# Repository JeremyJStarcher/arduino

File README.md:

# arduino
Random Arduino related things.

Some of these are better documented than others, but I figured it was better
to have one big repo rather than clutter things with a dozen small ones.

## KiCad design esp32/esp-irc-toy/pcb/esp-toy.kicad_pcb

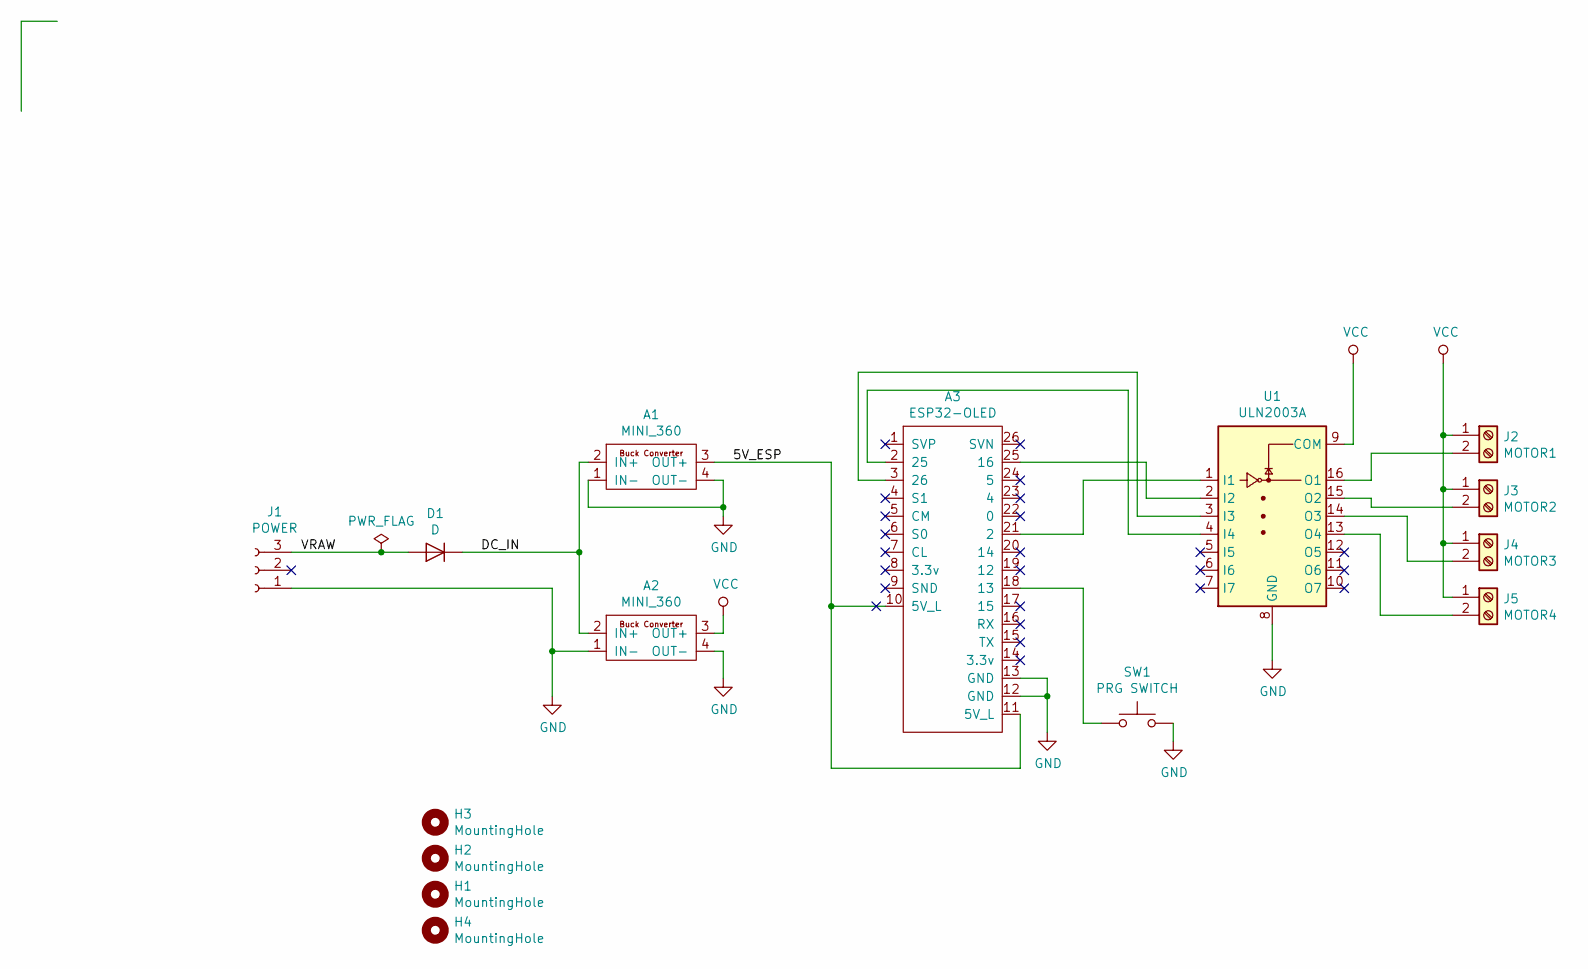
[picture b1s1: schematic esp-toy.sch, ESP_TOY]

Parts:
A1, A2: MINI_360
A3: ESP32-OLED
D1: D; D_5W_P12.70mm_Horizontal
H1, H2, H3, H4: MountingHole; MountingHole_2.2mm_M2_DIN965_Pad
J1: POWER; PinSocket_1x03_P2.54mm_Horizontal
J2: MOTOR1; TerminalBlock_bornier-2_P5.08mm
J3: MOTOR2; TerminalBlock_bornier-2_P5.08mm
J4: MOTOR3; TerminalBlock_bornier-2_P5.08mm
J5: MOTOR4; TerminalBlock_bornier-2_P5.08mm
SW1: PRG SWITCH; SW_PUSH-12mm
U1: ULN2003A; DIP-16_W10.16mm

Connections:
/5V_2: A1.3 (OUT+), A3.10 (5V_L), A3.11 (5V_L)
/DC_IN: A1.2 (IN+), A2.2 (IN+), D1.1 (K)
/VRAW: D1.2 (A), J1.3
GND: A1.1 (IN-), A1.4 (OUT-), A2.1 (IN-), A2.4 (OUT-), A3.12 (GND), A3.13 (GND), J1.1, SW1.2, U1.8 (GND)
unnamed: A3.2 (25), U1.4 (I4)
unnamed: A3.3 (26), U1.3 (I3)
unnamed: A3.18 (13), SW1.1
unnamed: A3.21 (2), U1.1 (I1)
unnamed: A3.25 (16), U1.2 (I2)
unnamed: J2.2, U1.16 (O1)
unnamed: J3.2, U1.15 (O2)
unnamed: J4.2, U1.14 (O3)
unnamed: J5.2, U1.13 (O4)
VCC: A2.3 (OUT+), J2.1, J3.1, J4.1, J5.1, U1.9 (COM)

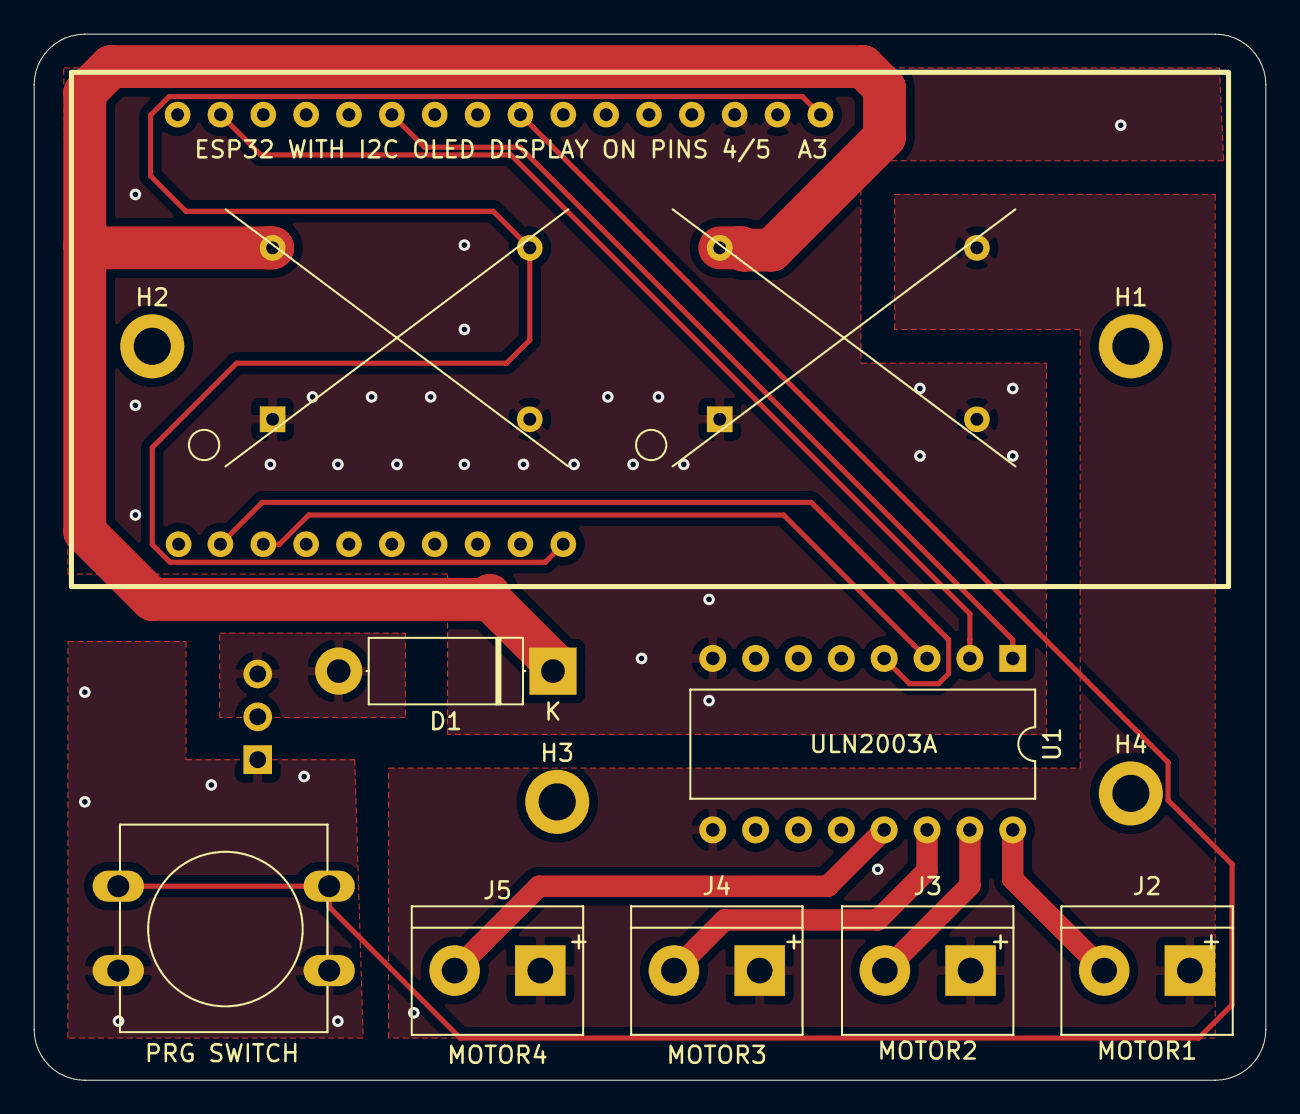
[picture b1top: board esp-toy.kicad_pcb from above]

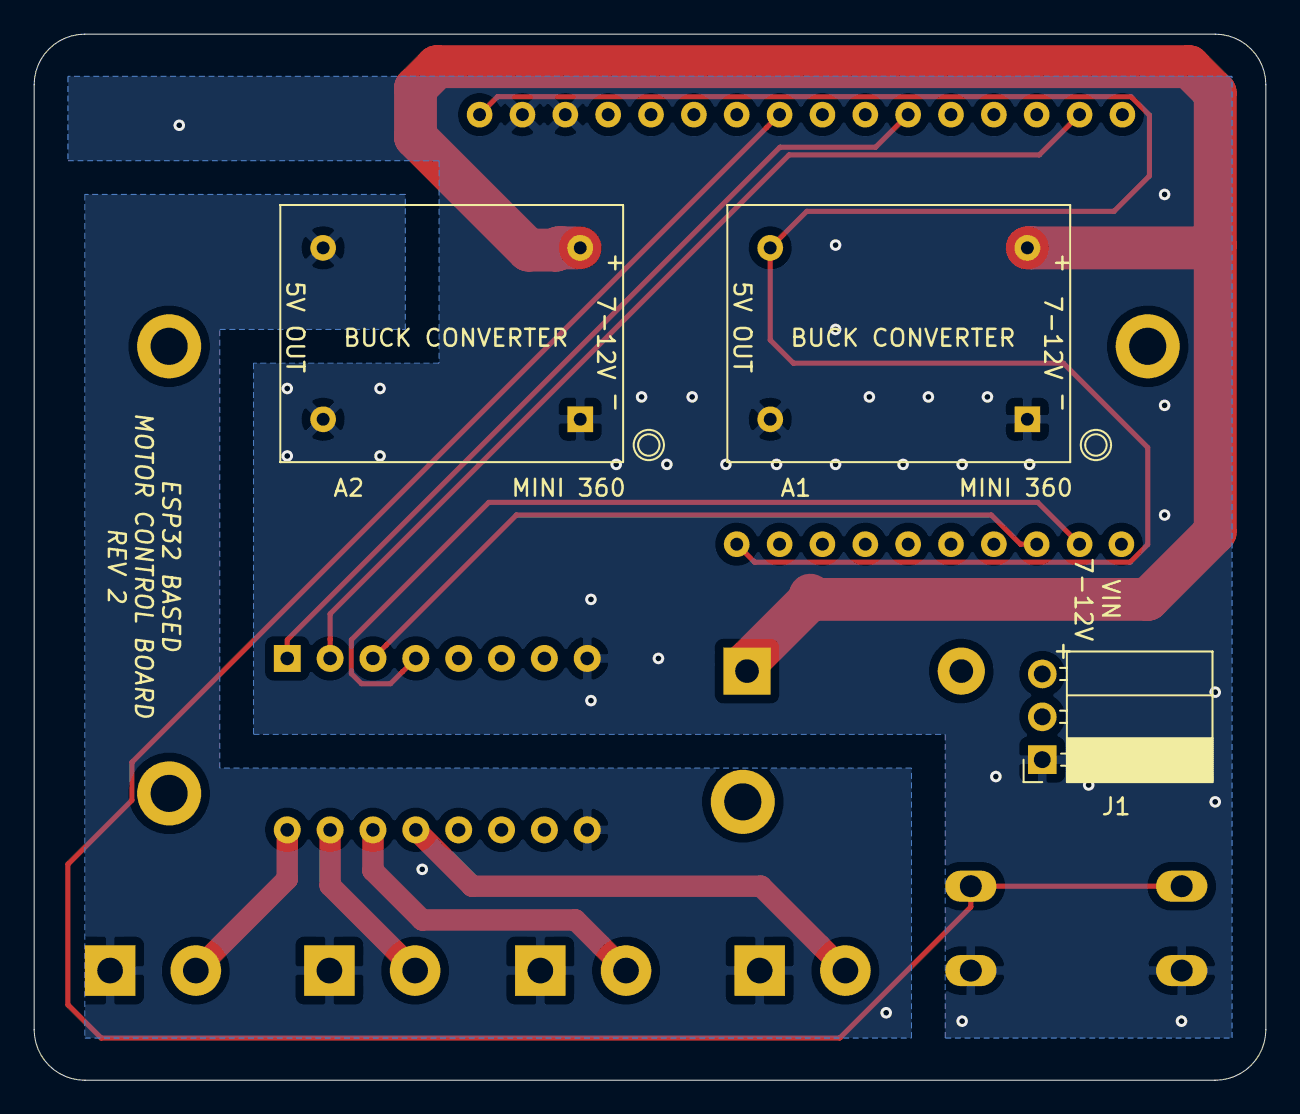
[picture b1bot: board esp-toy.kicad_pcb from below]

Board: 2 copper layers, 73.0 x 62.0 mm, 15 parts (3 on the bottom side), 14 nets.

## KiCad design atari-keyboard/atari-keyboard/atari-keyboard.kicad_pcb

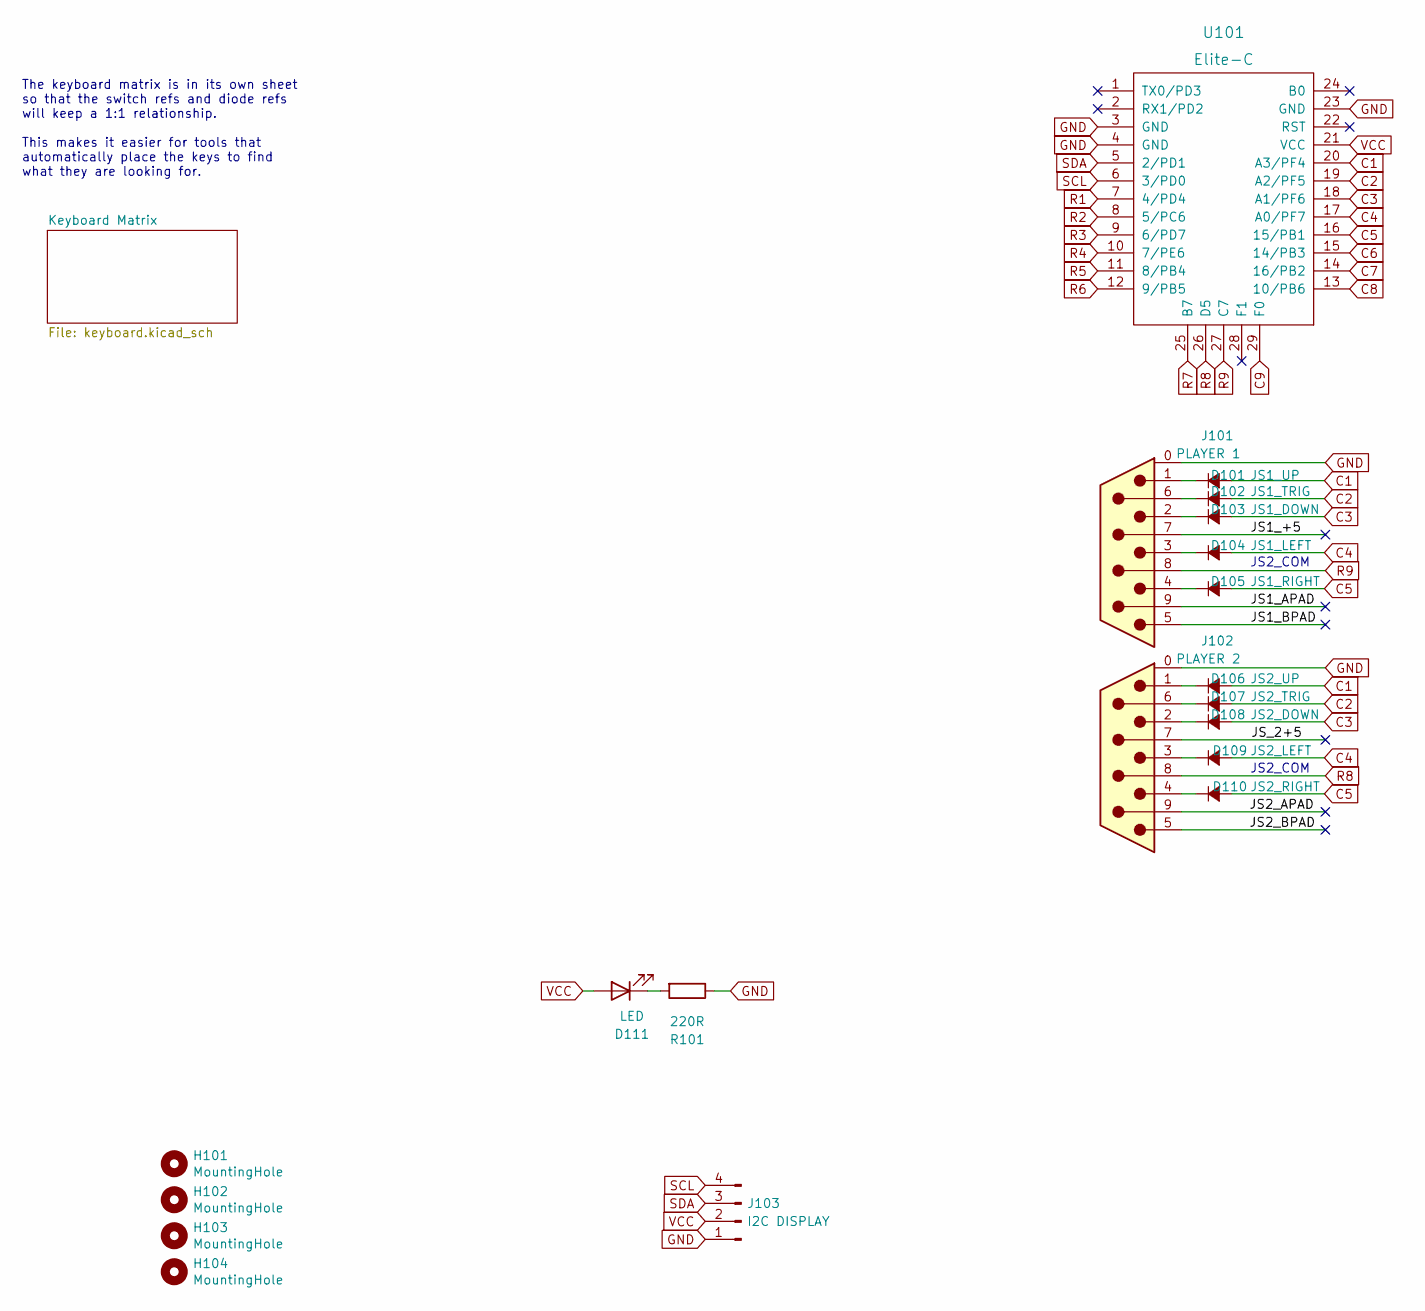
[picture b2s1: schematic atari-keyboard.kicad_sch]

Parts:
D101: JS1_UP; Diode-dual
D102: JS1_TRIG; Diode-dual
D103: JS1_DOWN; Diode-dual
D104: JS1_LEFT; Diode-dual
D105: JS1_RIGHT; Diode-dual
D106: JS2_UP; Diode-dual
D107: JS2_TRIG; Diode-dual
D108: JS2_DOWN; Diode-dual
D109: JS2_LEFT; Diode-dual
D110: JS2_RIGHT; Diode-dual
D111: LED; LED_D3.0mm
H101, H102, H103, H104: MountingHole; MountingHole_3.2mm_M3
J101: PLAYER 1; DSUB-9_Male_Horizontal_P2.77x2.84mm_EdgePinOffset9.90mm_Hou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
J102: PLAYER 2; DSUB-9_Male_Horizontal_P2.77x2.84mm_EdgePinOffset9.90mm_Hou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
J103: I2C DISPLAY; PinHeader_1x04_P2.54mm_Horizontal
R101: 220R; Resistor-Hybrid
U101: Elite-C; Elite-C-castellated-29pin-holes

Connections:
/JS1_+5: J101.7
/JS1_APAD: J101.9
/JS1_BPAD: J101.5
/JS2_APAD: J102.9
/JS2_BPAD: J102.5
/JS_2+5: J102.7
C1: D101.2 (A), D106.2 (A), U101.20 (A3/PF4); also elsewhere on the board
C2: D102.2 (A), D107.2 (A), U101.19 (A2/PF5); also elsewhere on the board
C3: D103.2 (A), D108.2 (A), U101.18 (A1/PF6); also elsewhere on the board
C4: D104.2 (A), D109.2 (A), U101.17 (A0/PF7); also elsewhere on the board
C5: D105.2 (A), D110.2 (A), U101.16 (15/PB1); also elsewhere on the board
C6: U101.15 (14/PB3); also elsewhere on the board
C7: U101.14 (16/PB2); also elsewhere on the board
C8: U101.13 (10/PB6); also elsewhere on the board
C9: U101.29 (F0); also elsewhere on the board
GND: J101.0 (GND), J102.0 (GND), J103.1, R101.1, U101.3 (GND), U101.4 (GND), U101.23 (GND)
unnamed: D101.1 (K), J101.1
unnamed: D102.1 (K), J101.6
unnamed: D103.1 (K), J101.2
unnamed: D104.1 (K), J101.3
unnamed: D105.1 (K), J101.4
unnamed: D106.1 (K), J102.1
unnamed: D107.1 (K), J102.6
unnamed: D108.1 (K), J102.2
unnamed: D109.1 (K), J102.3
unnamed: D110.1 (K), J102.4
unnamed: D111.1 (K), R101.2
R1: U101.7 (4/PD4); also elsewhere on the board
R2: U101.8 (5/PC6); also elsewhere on the board
R3: U101.9 (6/PD7); also elsewhere on the board
R4: U101.10 (7/PE6); also elsewhere on the board
R5: U101.11 (8/PB4); also elsewhere on the board
R6: U101.12 (9/PB5); also elsewhere on the board
R7: U101.25 (B7); also elsewhere on the board
R8: J102.8, U101.26 (D5); also elsewhere on the board
R9: J101.8, U101.27 (C7); also elsewhere on the board
SCL: J103.4, U101.6 (3/PD0)
SDA: J103.3, U101.5 (2/PD1)
VCC: D111.2 (A), J103.2, U101.21 (VCC)

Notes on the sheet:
JS2_COM
The keyboard matrix is in its own sheet so that the switch refs and diode refs will keep a 1:1 relationship. This makes it easier for tools that automatically place the keys to find what they are looking for.

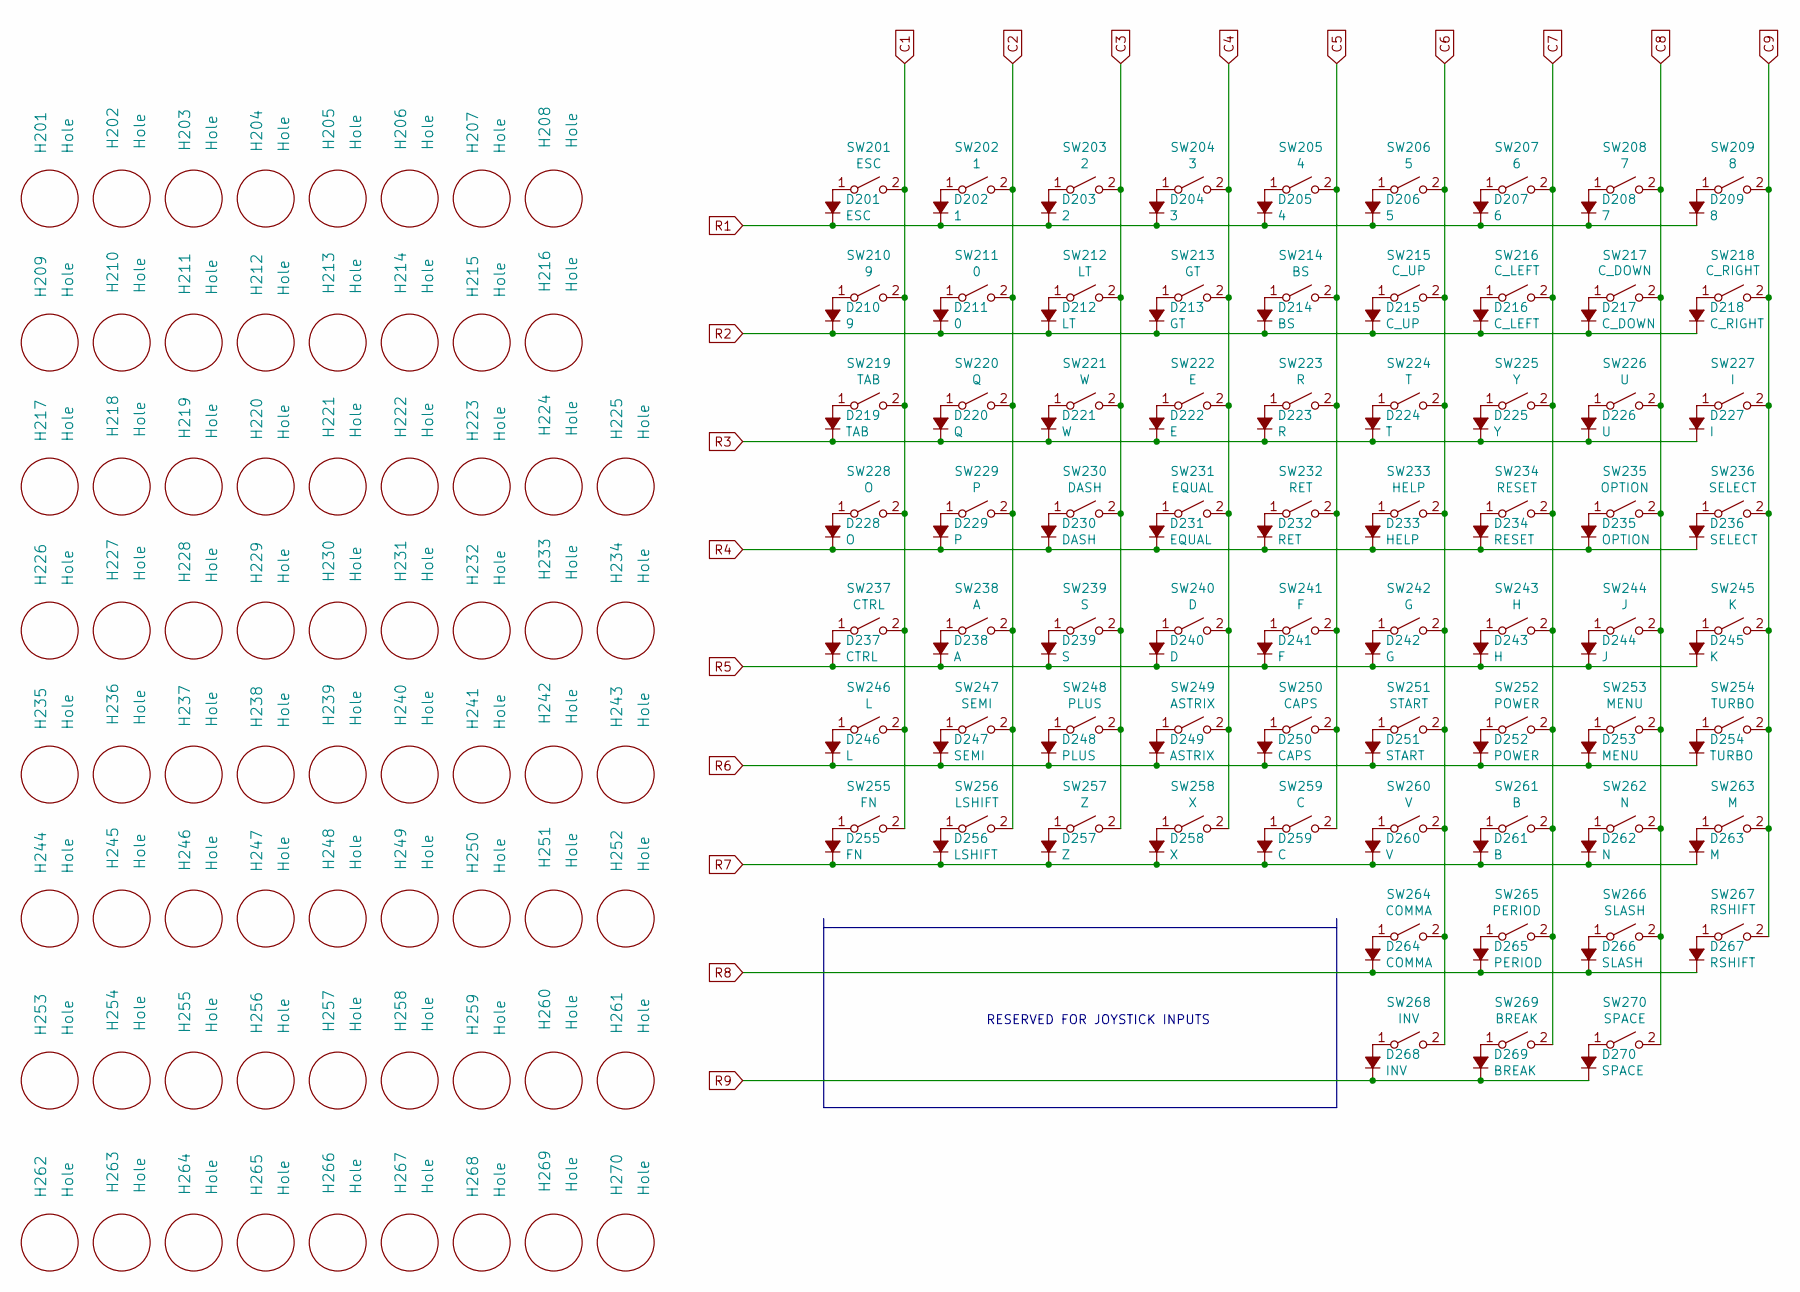
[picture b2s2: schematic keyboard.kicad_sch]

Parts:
D201: ESC; Diode-dual
D202: 1; Diode-dual
D203: 2; Diode-dual
D204: 3; Diode-dual
D205: 4; Diode-dual
D206: 5; Diode-dual
D207: 6; Diode-dual
D208: 7; Diode-dual
D209: 8; Diode-dual
D210: 9; Diode-dual
D211: 0; Diode-dual
D212: LT; Diode-dual
D213: GT; Diode-dual
D214: BS; Diode-dual
D215: C_UP; Diode-dual
D216: C_LEFT; Diode-dual
D217: C_DOWN; Diode-dual
D218: C_RIGHT; Diode-dual
D219: TAB; Diode-dual
D220: Q; Diode-dual
D221: W; Diode-dual
D222: E; Diode-dual
D223: R; Diode-dual
D224: T; Diode-dual
D225: Y; Diode-dual
D226: U; Diode-dual
D227: I; Diode-dual
D228: O; Diode-dual
D229: P; Diode-dual
D230: DASH; Diode-dual
D231: EQUAL; Diode-dual
D232: RET; Diode-dual
D233: HELP; Diode-dual
D234: RESET; Diode-dual
D235: OPTION; Diode-dual
D236: SELECT; Diode-dual
D237: CTRL; Diode-dual
D238: A; Diode-dual
D239: S; Diode-dual
D240: D; Diode-dual
D241: F; Diode-dual
D242: G; Diode-dual
D243: H; Diode-dual
D244: J; Diode-dual
D245: K; Diode-dual
D246: L; Diode-dual
D247: SEMI; Diode-dual
D248: PLUS; Diode-dual
D249: ASTRIX; Diode-dual
D250: CAPS; Diode-dual
D251: START; Diode-dual
D252: POWER; Diode-dual
D253: MENU; Diode-dual
D254: TURBO; Diode-dual
D255: FN; Diode-dual
D256: LSHIFT; Diode-dual
D257: Z; Diode-dual
D258: X; Diode-dual
D259: C; Diode-dual
D260: V; Diode-dual
D261: B; Diode-dual
D262: N; Diode-dual
D263: M; Diode-dual
D264: COMMA; Diode-dual
D265: PERIOD; Diode-dual
D266: SLASH; Diode-dual
D267: RSHIFT; Diode-dual
D268: INV; Diode-dual
D269: BREAK; Diode-dual
D270: SPACE; Diode-dual
H201, H202, H203, H204, H205, H206, H207, H208, H209, H210, H211, H212, H213, H214, H215, H216, H217, H218, H219, H220, H221, H222, H223, H224, H225, H226, H227, H228, H229, H230, H231, H232, H233, H234, H235, H236, H237, H238, H239, H240, H241, H242, H243, H244, H245, H246, H247, H248, H249, H250, H251, H252, H253, H254, H255, H256, H257, H258, H259, H260, H261, H262, H263, H264, H265, H266, H267, H268, H269, H270: Hole; MountingHole_2.2mm_M2
SW201: ESC; SW_Cherry_MX_1.25u_PCB
SW202: 1; SW_Cherry_MX_1.00u_PCB
SW203: 2; SW_Cherry_MX_1.00u_PCB
SW204: 3; SW_Cherry_MX_1.00u_PCB
SW205: 4; SW_Cherry_MX_1.00u_PCB
SW206: 5; SW_Cherry_MX_1.00u_PCB
SW207: 6; SW_Cherry_MX_1.00u_PCB
SW208: 7; SW_Cherry_MX_1.00u_PCB
SW209: 8; SW_Cherry_MX_1.00u_PCB
SW210: 9; SW_Cherry_MX_1.00u_PCB
SW211: 0; SW_Cherry_MX_1.00u_PCB
SW212: LT; SW_Cherry_MX_1.00u_PCB
SW213: GT; SW_Cherry_MX_1.00u_PCB
SW214: BS; SW_Cherry_MX_2.00u_PCB
SW215: C_UP; SW_Cherry_MX_1.00u_PCB
SW216: C_LEFT; SW_Cherry_MX_1.00u_PCB
SW217: C_DOWN; SW_Cherry_MX_1.00u_PCB
SW218: C_RIGHT; SW_Cherry_MX_1.00u_PCB
SW219: TAB; SW_Cherry_MX_1.75u_PCB
SW220: Q; SW_Cherry_MX_1.00u_PCB
SW221: W; SW_Cherry_MX_1.00u_PCB
SW222: E; SW_Cherry_MX_1.00u_PCB
SW223: R; SW_Cherry_MX_1.00u_PCB
SW224: T; SW_Cherry_MX_1.00u_PCB
SW225: Y; SW_Cherry_MX_1.00u_PCB
SW226: U; SW_Cherry_MX_1.00u_PCB
SW227: I; SW_Cherry_MX_1.00u_PCB
SW228: O; SW_Cherry_MX_1.00u_PCB
SW229: P; SW_Cherry_MX_1.00u_PCB
SW230: DASH; SW_Cherry_MX_1.00u_PCB
SW231: EQUAL; SW_Cherry_MX_1.00u_PCB
SW232: RET; SW_Cherry_MX_1.50u_PCB
SW233: HELP; SW_Cherry_MX_1.00u_PCB
SW234: RESET; SW_Cherry_MX_1.00u_PCB
SW235: OPTION; SW_Cherry_MX_1.00u_PCB
SW236: SELECT; SW_Cherry_MX_1.00u_PCB
SW237: CTRL; SW_Cherry_MX_2.00u_PCB
SW238: A; SW_Cherry_MX_1.00u_PCB
SW239: S; SW_Cherry_MX_1.00u_PCB
SW240: D; SW_Cherry_MX_1.00u_PCB
SW241: F; SW_Cherry_MX_1.00u_PCB
SW242: G; SW_Cherry_MX_1.00u_PCB
SW243: H; SW_Cherry_MX_1.00u_PCB
SW244: J; SW_Cherry_MX_1.00u_PCB
SW245: K; SW_Cherry_MX_1.00u_PCB
SW246: L; SW_Cherry_MX_1.00u_PCB
SW247: SEMI; SW_Cherry_MX_1.00u_PCB
SW248: PLUS; SW_Cherry_MX_1.00u_PCB
SW249: ASTRIX; SW_Cherry_MX_1.00u_PCB
SW250: CAPS; SW_Cherry_MX_1.25u_PCB
SW251: START; SW_Cherry_MX_1.00u_PCB
SW252: POWER; SW_Cherry_MX_1.00u_PCB
SW253: MENU; SW_Cherry_MX_1.00u_PCB
SW254: TURBO; SW_Cherry_MX_1.00u_PCB
SW255: FN; SW_Cherry_MX_1.75u_PCB
SW256: LSHIFT; SW_Cherry_MX_2.25u_PCB
SW257: Z; SW_Cherry_MX_1.00u_PCB
SW258: X; SW_Cherry_MX_1.00u_PCB
SW259: C; SW_Cherry_MX_1.00u_PCB
SW260: V; SW_Cherry_MX_1.00u_PCB
SW261: B; SW_Cherry_MX_1.00u_PCB
SW262: N; SW_Cherry_MX_1.00u_PCB
SW263: M; SW_Cherry_MX_1.00u_PCB
SW264: COMMA; SW_Cherry_MX_1.00u_PCB
SW265: PERIOD; SW_Cherry_MX_1.00u_PCB
SW266: SLASH; SW_Cherry_MX_1.00u_PCB
SW267: RSHIFT; SW_Cherry_MX_1.75u_PCB
SW268: INV; SW_Cherry_MX_1.00u_PCB
SW269: BREAK; SW_Cherry_MX_1.00u_PCB
SW270: SPACE; SW_Cherry_MX_6.25u_PCB

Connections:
C1: SW201.2 (B), SW210.2 (B), SW219.2 (B), SW228.2 (B), SW237.2 (B), SW246.2 (B), SW255.2 (B); also elsewhere on the board
C2: SW202.2 (B), SW211.2 (B), SW220.2 (B), SW229.2 (B), SW238.2 (B), SW247.2 (B), SW256.2 (B); also elsewhere on the board
C3: SW203.2 (B), SW212.2 (B), SW221.2 (B), SW230.2 (B), SW239.2 (B), SW248.2 (B), SW257.2 (B); also elsewhere on the board
C4: SW204.2 (B), SW213.2 (B), SW222.2 (B), SW231.2 (B), SW240.2 (B), SW249.2 (B), SW258.2 (B); also elsewhere on the board
C5: SW205.2 (B), SW214.2 (B), SW223.2 (B), SW232.2 (B), SW241.2 (B), SW250.2 (B), SW259.2 (B); also elsewhere on the board
C6: SW206.2 (B), SW215.2 (B), SW224.2 (B), SW233.2 (B), SW242.2 (B), SW251.2 (B), SW260.2 (B), SW264.2 (B), SW268.2 (B); also elsewhere on the board
C7: SW207.2 (B), SW216.2 (B), SW225.2 (B), SW234.2 (B), SW243.2 (B), SW252.2 (B), SW261.2 (B), SW265.2 (B), SW269.2 (B); also elsewhere on the board
C8: SW208.2 (B), SW217.2 (B), SW226.2 (B), SW235.2 (B), SW244.2 (B), SW253.2 (B), SW262.2 (B), SW266.2 (B), SW270.2 (B); also elsewhere on the board
C9: SW209.2 (B), SW218.2 (B), SW227.2 (B), SW236.2 (B), SW245.2 (B), SW254.2 (B), SW263.2 (B), SW267.2 (B); also elsewhere on the board
unnamed: D201.2 (A), SW201.1 (A)
unnamed: D202.2 (A), SW202.1 (A)
unnamed: D203.2 (A), SW203.1 (A)
unnamed: D204.2 (A), SW204.1 (A)
unnamed: D205.2 (A), SW205.1 (A)
unnamed: D206.2 (A), SW206.1 (A)
unnamed: D207.2 (A), SW207.1 (A)
unnamed: D208.2 (A), SW208.1 (A)
unnamed: D209.2 (A), SW209.1 (A)
unnamed: D210.2 (A), SW210.1 (A)
unnamed: D211.2 (A), SW211.1 (A)
unnamed: D212.2 (A), SW212.1 (A)
unnamed: D213.2 (A), SW213.1 (A)
unnamed: D214.2 (A), SW214.1 (A)
unnamed: D215.2 (A), SW215.1 (A)
unnamed: D216.2 (A), SW216.1 (A)
unnamed: D217.2 (A), SW217.1 (A)
unnamed: D218.2 (A), SW218.1 (A)
unnamed: D219.2 (A), SW219.1 (A)
unnamed: D220.2 (A), SW220.1 (A)
unnamed: D221.2 (A), SW221.1 (A)
unnamed: D222.2 (A), SW222.1 (A)
unnamed: D223.2 (A), SW223.1 (A)
unnamed: D224.2 (A), SW224.1 (A)
unnamed: D225.2 (A), SW225.1 (A)
unnamed: D226.2 (A), SW226.1 (A)
unnamed: D227.2 (A), SW227.1 (A)
unnamed: D228.2 (A), SW228.1 (A)
unnamed: D229.2 (A), SW229.1 (A)
unnamed: D230.2 (A), SW230.1 (A)
unnamed: D231.2 (A), SW231.1 (A)
unnamed: D232.2 (A), SW232.1 (A)
unnamed: D233.2 (A), SW233.1 (A)
unnamed: D234.2 (A), SW234.1 (A)
unnamed: D235.2 (A), SW235.1 (A)
unnamed: D236.2 (A), SW236.1 (A)
unnamed: D237.2 (A), SW237.1 (A)
unnamed: D238.2 (A), SW238.1 (A)
unnamed: D239.2 (A), SW239.1 (A)
unnamed: D240.2 (A), SW240.1 (A)
unnamed: D241.2 (A), SW241.1 (A)
unnamed: D242.2 (A), SW242.1 (A)
unnamed: D243.2 (A), SW243.1 (A)
unnamed: D244.2 (A), SW244.1 (A)
unnamed: D245.2 (A), SW245.1 (A)
unnamed: D246.2 (A), SW246.1 (A)
unnamed: D247.2 (A), SW247.1 (A)
unnamed: D248.2 (A), SW248.1 (A)
unnamed: D249.2 (A), SW249.1 (A)
unnamed: D250.2 (A), SW250.1 (A)
unnamed: D251.2 (A), SW251.1 (A)
unnamed: D252.2 (A), SW252.1 (A)
unnamed: D253.2 (A), SW253.1 (A)
unnamed: D254.2 (A), SW254.1 (A)
unnamed: D255.2 (A), SW255.1 (A)
unnamed: D256.2 (A), SW256.1 (A)
unnamed: D257.2 (A), SW257.1 (A)
unnamed: D258.2 (A), SW258.1 (A)
unnamed: D259.2 (A), SW259.1 (A)
unnamed: D260.2 (A), SW260.1 (A)
unnamed: D261.2 (A), SW261.1 (A)
unnamed: D262.2 (A), SW262.1 (A)
unnamed: D263.2 (A), SW263.1 (A)
unnamed: D264.2 (A), SW264.1 (A)
unnamed: D265.2 (A), SW265.1 (A)
unnamed: D266.2 (A), SW266.1 (A)
unnamed: D267.2 (A), SW267.1 (A)
unnamed: D268.2 (A), SW268.1 (A)
unnamed: D269.2 (A), SW269.1 (A)
unnamed: D270.2 (A), SW270.1 (A)
R1: D201.1 (K), D202.1 (K), D203.1 (K), D204.1 (K), D205.1 (K), D206.1 (K), D207.1 (K), D208.1 (K), D209.1 (K); also elsewhere on the board
R2: D210.1 (K), D211.1 (K), D212.1 (K), D213.1 (K), D214.1 (K), D215.1 (K), D216.1 (K), D217.1 (K), D218.1 (K); also elsewhere on the board
R3: D219.1 (K), D220.1 (K), D221.1 (K), D222.1 (K), D223.1 (K), D224.1 (K), D225.1 (K), D226.1 (K), D227.1 (K); also elsewhere on the board
R4: D228.1 (K), D229.1 (K), D230.1 (K), D231.1 (K), D232.1 (K), D233.1 (K), D234.1 (K), D235.1 (K), D236.1 (K); also elsewhere on the board
R5: D237.1 (K), D238.1 (K), D239.1 (K), D240.1 (K), D241.1 (K), D242.1 (K), D243.1 (K), D244.1 (K), D245.1 (K); also elsewhere on the board
R6: D246.1 (K), D247.1 (K), D248.1 (K), D249.1 (K), D250.1 (K), D251.1 (K), D252.1 (K), D253.1 (K), D254.1 (K); also elsewhere on the board
R7: D255.1 (K), D256.1 (K), D257.1 (K), D258.1 (K), D259.1 (K), D260.1 (K), D261.1 (K), D262.1 (K), D263.1 (K); also elsewhere on the board
R8: D264.1 (K), D265.1 (K), D266.1 (K), D267.1 (K); also elsewhere on the board
R9: D268.1 (K), D269.1 (K), D270.1 (K); also elsewhere on the board

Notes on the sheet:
RESERVED FOR JOYSTICK INPUTS

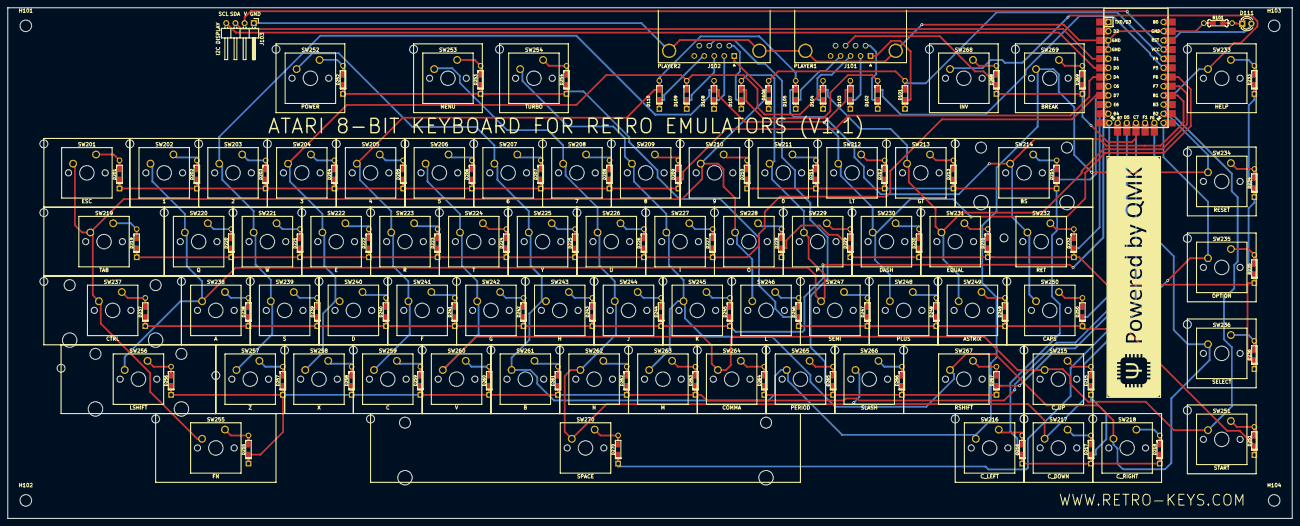
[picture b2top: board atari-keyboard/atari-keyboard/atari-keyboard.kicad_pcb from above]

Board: 2 copper layers, 355.8 x 141.4 mm, 230 parts (0 on the bottom side), 103 nets.

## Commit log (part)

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2019-10-17 Files moved from old repo to this one.
2019-10-17 Added pro-micro-blink
2019-10-18 First commit of the serial-crc
2019-10-18 Cleaned up tests to add better logging
2019-10-18 Ensure IoSerial read/write works
    And added tests
2019-10-18 Dejanked the tests so they are clean
2019-10-18 Added flush tests
    and discovered sign problems, so I resolved those too
2019-10-19 Added master and slave role
    So that two boards can get the same sketch then do the Right Thing(tm)
2019-10-19 Clean up xmodem code
2019-10-19 XModem transfer works between two arduinos
    Master/slave setting now controlled by jumpers rather than EEPROM
    Master resets slave device to keep them in sync.
2019-10-19 renamed xmodem to xmodem-old
2019-10-19 Code works -- at least until looking to end the broadcast
2019-10-20 Moved block of code more to fit with code path
2019-10-20 removed extra white space
2019-10-20 Flagged OldXmodem stuff and removed duplicate code
2019-10-20 Temp commit
2019-10-21 too many changes.
    Added code to check the message was trasmitted correctly.
    Put a bunch of string literals in F() macros.
    Added blinking the builtin LED to show success or failure.
2019-10-21 Testing variable length messages
    Messages cross a packet size boundary. We make sure that the incoming
    data is exactly as we expect and that we don't have a buffer overrun
    error.
2019-10-21 White space cleanup
2019-10-21 Bumped up BAUD rate
2019-10-21 xmodem state and status behind a getter
    Set up a common 'init_frame' method
2019-10-22 Data transfer both ways working
    LOTS of debugging code still scattered about though.
2019-10-22 Added hardware handshaking between tests
    Make sure the two system are kept in time in case post-test
    processing ends up taing a while.
2019-10-22 Reworked calling process of tests
    Each test is self contained with a 'master' branch and a 'slave'
    branch, rather than having two lists of tests -- one for 'master'
    and one for 'slave.'
2019-10-22 Added New to New transfers
2019-10-23 Made the loop back tests opt-in
    Since it requires four serial ports to actually run and you can't
    use all soft-serial libraries for it.
2019-10-23 Sending New2Old - damaged packets are resent properly
2019-10-24 Displaying the full activity of old-to-old transfers
2019-10-25 NEW to OLD works
2019-10-27 Added case for Oriana's scrolling LED sign
2019-10-27 Included xmodem code and cleaned up compile errors
2019-10-28 Renamed 'test' to 'runner'
    Since it didn't actually hold any tests.
2019-10-28 Dead code cleanup.
2019-10-29 Kick font size to readable
2019-10-30 Injected I/O calls into xmodem routines
    This generalizes the I/O handling so we can use it with any serial link.
2019-10-31 Removed unneeded initialization code
    Lets just rely on xmodem to sync itself...
2019-10-31 Added the 'changed packet' and 'inserted byte' glitch to tests
    :
2019-11-01 Replaced some formulas with hard-coded constants.
2019-11-02 Brought over the Portal Badge
    updated the code to compile on more modern libraries
    Added 3D printed badge to wear
2019-11-03 Calculate checksomes on the fly while sending
2019-11-03 removed last traces of internal buffer
    The internal buffers are no longer used at all.
    Checksomes calculated on the fly during send and receive
2019-11-04 transfers now working properly on the MEGA
2019-11-06 put the xmodem logging behind a define
2019-11-07 Turned the xmodem transfer results into an class enum
2019-11-08 Added receiving in character mode
2019-11-09 Re-arranged some constants to cleanup code
2019-11-09 More code cleanup of includes and defines
2019-11-09 Clarified the use of `this->`
2019-11-09 Renamed a couple of functions to get ready to add a new variant of them
2019-11-10 Got rid of unneeded LOG statements
2019-11-10 Removed external logging code
2019-11-10 Added a explanation comment behind an edge case handling
2019-11-10 The minicom won't fire if compiled code fails
2019-11-10 Fixed a compile error given by G++ in strict mode
    We weren't returning a value, so change the function prototype
2019-11-11 Trying to declutter un-needed junk.
2019-11-11 Updated baud rate for tests
2019-11-11 Removed dead code
2019-11-11 Timed the tests
2019-11-16 Set BAUD rate to reasonable level that works
2019-11-16 Giving slave a chance to reprogram for reset
2019-11-16 Cleaned up the tryChar with initState
    Got away from hard-coded constants and a better explanation of what is
    going on.
2019-11-16 Removed old code
2019-11-16 Pass around the full packet number, not just the wrapped around version.
2019-11-16 Cleaned up a bit of the code
2019-11-17 Added a STREAM based constructor on the XModem object.
    This means the user won't need to wrap a stream object up, but I kept
    the old API as well so it can be used with non-stream objects as well.
2019-11-19 Moved defines to constants
2019-11-19 Removed unneeded function parameter
2019-11-23 Added a buffer-by-buffer mode
2019-11-23 Extracted out just the conditions needed for buffered transfor for clarity.
2019-11-23 Cleaned up some logic, got rid of some branching
2020-07-04 Updated code
2020-07-05 Password and lock screen in place
2020-07-05 Able to turn screen off.
2020-07-07 Device running on board
    Reversed 12-button keypad
    Cleaned up how the menu worked
2020-07-18 Added saved projects.
2020-07-29 Added/moved ESP32 examples
2020-08-03 Many, many changes --
    Brought in the local IRC library so I could tweak it.
    Multiple things to control.
    PWM support
    better command line
2020-08-03 Moved the AP stuff into its own file
2020-08-03 Resolved issue of crash when inssuing a bad 'set' command
2020-08-03 Dead code removal
2020-08-04 Detects IRC login and gives status updates
2020-08-06 Highlight things on screen
2020-08-06 Removed the feeper
2020-08-06 Changed intensity to 'high' 'medium' 'low' instead of a number.
2020-08-06 Allowed 'h' 'm' or 'l' for intensity
2020-09-15 Sample flicker-flame code
2020-09-16 Uses the user config server info. Inits the OLED screen earlier.
2020-11-09 Updating
2020-11-14 Updated atarikeyboard shift and FN key
2020-12-13 Reworked some minor things for tests
2020-12-13 Added the PWM calculator for raw atmel calc
2020-12-13 Setting up programming mode.
2020-12-13 Saving text to type, cleaned up a bunch of warnings
2020-12-13 Basic text is typed when key is pressed
2021-04-09 random stuff
2021-04-12 Stole ESP32 phone camera remote shutter
2021-10-10 Added arrow keys and joystick support. Writing code to auto-calc key placement.
2021-10-11 Rendered basic SVG version of the keyboard
2021-10-11 LOTS of code cleanup and better handling of setting keycap labels.
2021-10-11 Added code to rip the font out into nice reusable SVG files for each character.
2021-10-17 Added joystick ports to Atari keyboard schematic
2021-10-17 bunch of work done to the wifi monitor to make it functional
2021-10-17 Moved the ripper code out of the Atari keyboard project cause I gave up on that approach
2021-10-18 Added icons for the four suits of cards
2021-10-20 Made keyboard layout a little bit more pretty
2021-10-23 Brought in the new version of the Key library from github
2021-10-24 The keyboard is being generated nicely with embedded graphics.
2021-10-24 Removed dead files no longer needed
2021-10-24 Python update
2021-10-24 added output-files to git-ignore
2021-10-24 Moved SVG files we stoe from
2021-10-24 Rename a file to make it clearer what it does
2021-10-24 Bump y18n in /atari-keyboard/layout-code/layout-code-py/scad/KeyV2
    Bumps [y18n](https://github.com/yargs/y18n) from 3.2.1 to 3.2.2.
    - [Release notes](https://github.com/yargs/y18n/releases)
    - [Changelog](https://github.com/yargs/y18n/blob/master/CHANGELOG.md)
    - [Commits](https://github.com/yargs/y18n/commits)
    ---
    updated-dependencies:
2021-10-24 Bump path-parse in /atari-keyboard/layout-code/layout-code-py/scad/KeyV2
    Bumps [path-parse](https://github.com/jbgutierrez/path-parse) from 1.0.6 to 1.0.7.
    - [Release notes](https://github.com/jbgutierrez/path-parse/releases)
    - [Commits](https://github.com/jbgutierrez/path-parse/commits/v1.0.7)
    ---
    updated-dependencies:
    - dependency-name: path-parse
2021-10-25 Lots of changes from testing, mostly making the s-expression parser into its own library
2021-11-11 Added the ability to have many tokens inside of an expression.
2021-11-11 Added the ability to read quoted strings.
2021-11-11 Cleaned up some typing errors we collected along the way
2022-04-18 kicad 6
2022-08-13 Cleaning up dead files
2022-08-13 Stripped out some old KiCad6 test versions
2022-08-15 Cleaned up files and resaved
2022-08-20 Added keycap generator
2022-08-21 Added the rest of the keycap graphics.
2022-08-21 Fixed typo of missing semicolon
2022-08-21 Added fulllayout to build scripts
2022-08-21 Changed font and make key inset deeper
2022-08-21 Rendering pre-tilted keys
2022-08-22 Added keybump to 'F' and 'J' keys
2022-08-22 Added thicker walls tot he grid keys so that support can be applied.
2022-08-22 Changed tilt of rendered keys to 25 degrees
2022-08-23 Renamed 'rshift' to 'key_rshift'
2022-08-23 Removed debugging 'echo'
2022-08-23 More code cleanup and fixed malformed grid keys and fixed offset of supports.
2022-08-23 Fixed the 'backspace' and 'fn' key text/size
2022-08-25 Re-enforced supports -- again -- and added rotation.
2022-08-26 Moved keyboard-layout-editor code
2022-11-12 Bump minimatch in /atari-keyboard/layout-code/layout-code-py/scad/KeyV2
    Bumps [minimatch](https://github.com/isaacs/minimatch) from 3.0.4 to 3.1.2.
    - [Release notes](https://github.com/isaacs/minimatch/releases)
    - [Commits](https://github.com/isaacs/minimatch/compare/v3.0.4...v3.1.2)
    ---
    updated-dependencies:
    - dependency-name: minimatch
2022-11-25 reworked keycaps for fdm printing
2022-11-26 Did the new keyboard layout.
2022-11-27 Front silk screen added for all keys.
2022-11-27 Switched over to hybrid resisters and diodes.
2022-11-28 Bounding box of circuit board calculated
2022-11-28 mounting holes in place
2022-11-29 Before python scripts
2022-11-29 Lots of work done to the python
2022-11-30 Fix the key position.
2022-11-30 bounding boxes working -- taken from user drawings.
2022-12-07 Bump decode-uri-component
    Bumps [decode-uri-component](https://github.com/SamVerschueren/decode-uri-component) from 0.2.0 to 0.2.2.
    - [Release notes](https://github.com/SamVerschueren/decode-uri-component/releases)
    - [Commits](https://github.com/SamVerschueren/decode-uri-component/compare/v0.2.0...v0.2.2)
    ---
    updated-dependencies:
    - dependency-name: decode-uri-component
2022-12-09 Added a software switch between fdm and resin printing and cleaned up row issue.
2022-12-11 Added MX data sheet
2022-12-11 Added the keyboard mounting hole offsets.
2022-12-12 Draw exclusion zones around mounting holes.
2022-12-13 Cleaned up use of find objects by noun.
2022-12-14 Lets make binary STLs
2022-12-15 more cleanup
2022-12-18 Fixed y-positional handling in BOM export.
2022-12-19 Fixed various rendering issues.
2022-12-21 Changed stem support type. MUCH better FDM prints.
2022-12-21 Added 3d printable tools.
2022-12-24 Changed font sizes for better prints.
2022-12-24 Added the keyswitch 3d models
2022-12-24 Grabbed files missed in earlier commmits
2022-12-24 Fixed the size of the LSHIFT
2022-12-24 Resolved a number of issues of keycaps not rendering correctly
2022-12-24 Brought in freeRouting shortcut.
2022-12-24 Re-routed board after fixing schematic
2022-12-24 Changed I2C connector on-board labeling
2022-12-25 Cleaned up some routing and added QMK logo
2023-05-16 Code compiles again and config data is preserved in a round-trip to the front end
2023-05-20 Added cable protector to case design
